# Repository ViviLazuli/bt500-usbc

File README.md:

# bt500-usbc
### USB Type-C mod for the BT-500 bluetooth adapter

A USB C mod board for the Handheld Scientific BT-500 Bluetooth keyboard & mouse adapter,
featuring enhanced mounting and high-current capabilities.

### Features
- USB C host port and peripheral port
- M2 mounting holes
- High-current power traces bypassing the BT-500 for increased power delivery to peripherals
- 500 mA or 1.5 A peripheral current setting

### Instructions
1. Get a copy of the board, or use oshpark or jlcpcb to manufacture it.
2. Get the necessary components.
3. Assemble the board and test it.
4. Optionally, laser cut a sandwich-style case for the adapter.

`made w/ 💜 by vivi, 2020`

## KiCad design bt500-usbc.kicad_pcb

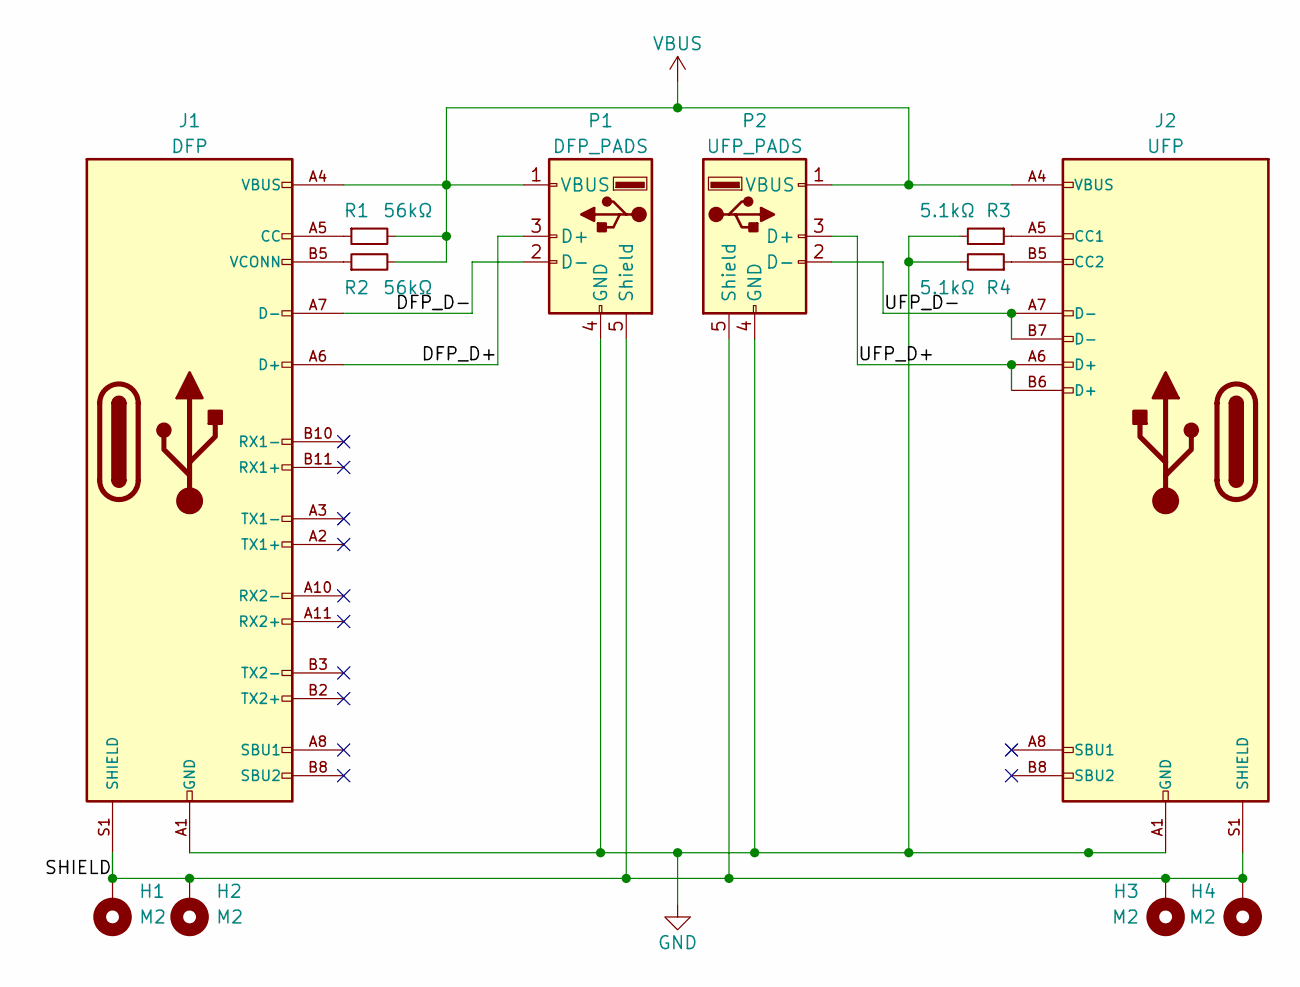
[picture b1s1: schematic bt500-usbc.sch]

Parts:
H1, H2, H3, H4: M2; MountingHole_2.2mm_M2_Pad
J1: DFP; HIROSE_CX60-24S-UNIT; Part No. CX60-24S-UNIT
J2: UFP; HRS_CX90M-16P; Part No. CX90M-16P
P1: DFP_PADS; USB_A_FP
P2: UFP_PADS; USB_A_FP
R1, R2: 56kΩ; R_0805_2012Metric_Pad1.15x1.40mm_HandSolder
R3, R4: 5.1kΩ; R_0805_2012Metric_Pad1.15x1.40mm_HandSolder

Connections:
/DFP_D+: J1.A6 (D+), P1.3 (D+)
/DFP_D-: J1.A7 (D-), P1.2 (D-)
/SHIELD: H1.1, H2.1, H3.1, H4.1, J1.S1 (SHIELD), J1.S2 (SHIELD1), J1.S3 (SHIELD2), J1.S4 (SHIELD2), J2.S1 (SHIELD), J2.S2 (SHIELD), J2.S3 (SHIELD), J2.S4 (SHIELD), P1.5 (Shield), P2.5 (Shield)
/UFP_D+: J2.A6 (D+), J2.B6 (D+), P2.3 (D+)
/UFP_D-: J2.A7 (D-), J2.B7 (D-), P2.2 (D-)
GND: J1.A1 (GND), J1.A12 (GNDA), J1.B1 (GNDB), J1.B12 (GNDB), J2.A1 (GND), J2.A12 (GNDA2), J2.B1 (GNDB1), J2.B12 (GNDB2), J2.MID1 (MID), J2.MID2 (MID), P1.4 (GND), P2.4 (GND), R3.2, R4.2
unnamed: J1.A5 (CC), R1.1
unnamed: J1.B5 (VCONN), R2.1
unnamed: J2.A5 (CC1), R3.1
unnamed: J2.B5 (CC2), R4.1
VBUS: J1.A4 (VBUS), J1.A9 (VBUS_A), J1.B4 (VBUS_B), J1.B9 (VBUS_B), J2.A4 (VBUS), J2.A9 (VBUSA2), J2.B4 (VBUSB1), J2.B9 (VBUSB2), P1.1 (VBUS), P2.1 (VBUS), R1.2, R2.2

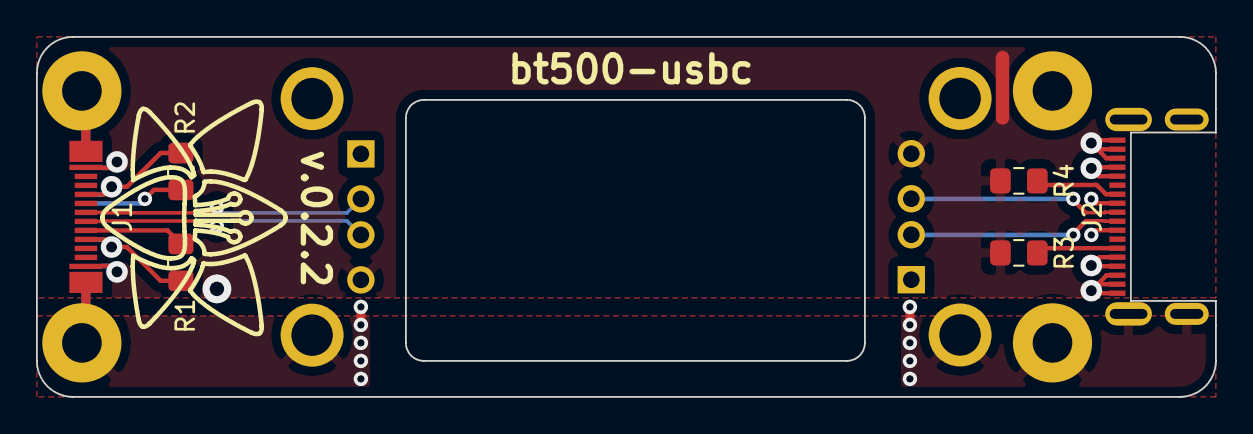
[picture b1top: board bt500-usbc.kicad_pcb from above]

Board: 4 copper layers, 65.5 x 20.0 mm, 12 parts (0 on the bottom side), 11 nets.
